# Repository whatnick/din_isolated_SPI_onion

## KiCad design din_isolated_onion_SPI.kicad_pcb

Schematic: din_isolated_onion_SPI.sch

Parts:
C1, C2, C3: 100nF; C_0603_1608Metric
D1, D2, D3, D4, D5, D6: LED; LED_0603_1608Metric
DONE1: TestPoint; TestPoint_THTPad_D1.0mm_Drill0.5mm
FW_RST1: TestPoint; TestPoint_Pad_1.5x1.5mm
GP11, GP15, GP16, GP17, GP18, GP19: TestPoint; TestPoint_THTPad_D1.0mm_Drill0.5mm
J1, J2: Conn_01x16; PinSocket_1x16_P2.54mm_Vertical
J3: Conn_01x10; Molex_Micro-Latch_53253-1070_1x10_P2.00mm_Vertical
J4: Test_Power_Bridge; PinHeader_2x02_P2.54mm_Vertical
LOGO1: Logo_Open_Hardware_Large; OSHW-Logo2_7.3x6mm_SilkScreen
MET_SEL1: MET_S; TestPoint_THTPad_D1.0mm_Drill0.5mm
R1: 29.4K; R_0603_1608Metric
R2, R3, R4, R5, R6, R7: 330R; R_0603_1608Metric
RST1: Jumper_2_Open; SolderJumper-2_P1.3mm_Open_Pad1.0x1.5mm
U1: Omega2+; Onion_Omega2+
U2: SI8661AB-B-IS1; SOIC127P600X175-16N
U3: TPL5010-Q1; TSOT-23-6
U4: 74LVC125; TSSOP-14_4.4x5mm_P0.65mm
U5: NL7SZ19; SOT-23-6
VCC1: Jumper_2_Bridged; SolderJumper-2_P1.3mm_Bridged_Pad1.0x1.5mm
WAKE1: TestPoint; TestPoint_THTPad_D1.0mm_Drill0.5mm

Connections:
3V3_C: C1.1, C3.1, J1.1, J3.1, J4.3, U1.31, U2.1, U3.1, U4.14 (VCC), U5.5, VCC1.1
3V3_I: C2.1, J3.10, J4.4, U2.16
3V3_O: J1.2, U1.25, VCC1.2
/GP11: D1.2, GP11.1, J1.3, U1.2
/GP15: D4.2, GP15.1, J1.6, U1.7
/GP16: D3.2, GP16.1, J1.5, U1.6
/GP17: D2.2, GP17.1, J1.4, U1.5
/GP18: D6.2, GP18.1, J1.8, U1.20
/GP19: D5.2, GP19.1, J1.7, U1.19
CLK_E: J3.5, U2.15
CLK_O: U1.12, U2.2
CS0_E: J3.4, U2.13
CS0_O: U1.13, U5.1
CS1_E: J3.8, U2.12
CS2_E: J3.3, U2.11
CSMUX_0: U2.4, U4.1, U5.6
CSMUX_1: U2.5, U4.4, U5.4
CS_SPARE: U2.6, U4.10
GND_C: C1.2, C3.2, J1.15, J1.16, J3.2, J4.1, R1.1, R2.2, R3.2, R4.2, R5.2, R6.2, R7.2, U1.1, U1.32, U2.8, U3.2, U4.7 (GND), U5.2
GND_I: C2.2, J3.9, J4.2, U2.9
MISO_E: J3.6, U2.10
MISO_O: U1.10
MISO_O_ISO: U2.7, U4.2, U4.5, U4.9
MOSI_E: J3.7, U2.14
MOSI_O: U1.11, U2.3
unnamed: D1.1, R2.1
unnamed: D2.1, R3.1
unnamed: D3.1, R4.1
unnamed: D4.1, R5.1
unnamed: D5.1, R6.1
unnamed: D6.1, R7.1
unnamed: DONE1.1, U3.4
unnamed: FW_RST1.1, U1.26
unnamed: J1.9, U1.3
unnamed: J1.10, U1.4
unnamed: J1.11, U1.14
unnamed: J1.12, U1.15
unnamed: J2.2, U1.28
unnamed: J2.3, U1.27
unnamed: J2.6, U1.9
unnamed: J2.7, U1.8
unnamed: J2.8, U1.24
unnamed: J2.9, U1.23
unnamed: J2.10, U1.22
unnamed: J2.11, U1.21
unnamed: J2.14, U1.18
unnamed: J2.15, U1.17
unnamed: MET_SEL1.1, U5.3
unnamed: R1.2, U3.3
unnamed: RST1.1, U3.6
unnamed: U3.5, WAKE1.1
unnamed: U4.3, U4.6, U4.8
U_D+: J2.4, U1.30
U_D-: J2.5, U1.29
~RST: J2.1, RST1.2, U1.16

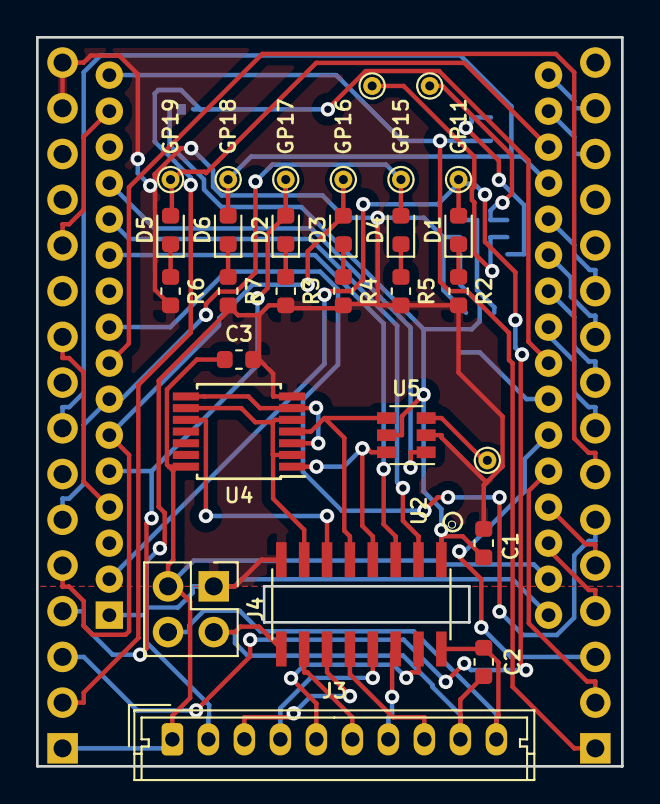
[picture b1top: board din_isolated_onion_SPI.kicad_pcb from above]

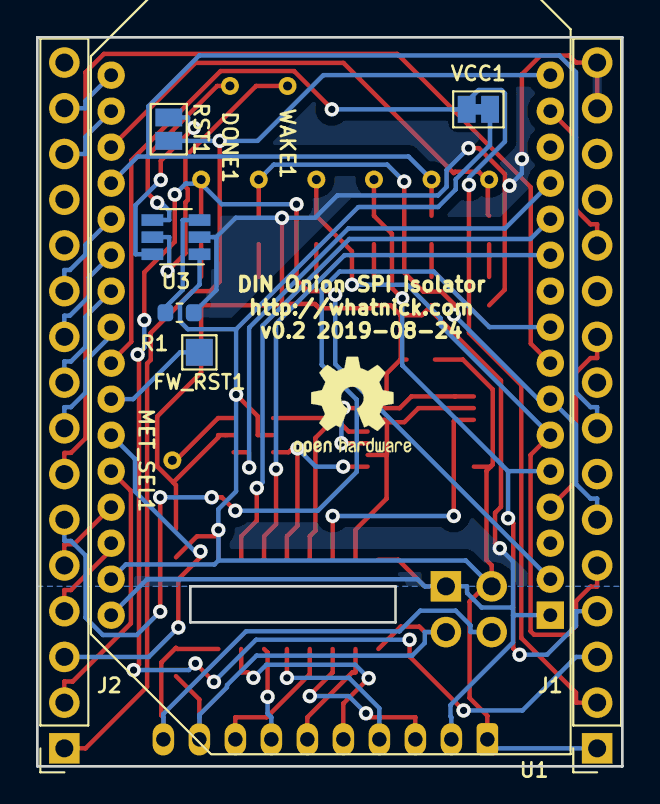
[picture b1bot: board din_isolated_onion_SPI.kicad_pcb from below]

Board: 4 copper layers, 32.5 x 40.5 mm, 38 parts (9 on the bottom side), 54 nets.

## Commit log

2019-06-27 Initial import
2019-06-28 Add pads and renders
2019-06-29 Add GPIO-CS Mux pins
2019-06-29 Add reset IC and finalize test points
2019-06-30 Finalize v0.1 routing
2019-06-30 Switch to TSOT for hardware reset
2019-08-17 Add quad buffer and GPIO LED's
2019-08-18 Add 1x2 Demux symbol to share CS pin
2019-08-19 Move parts into place on PCB for route
2019-08-21 Partially complete routing
2019-08-24 Complete route with x4 layers
2019-08-24 Clean up silkscreen and render
